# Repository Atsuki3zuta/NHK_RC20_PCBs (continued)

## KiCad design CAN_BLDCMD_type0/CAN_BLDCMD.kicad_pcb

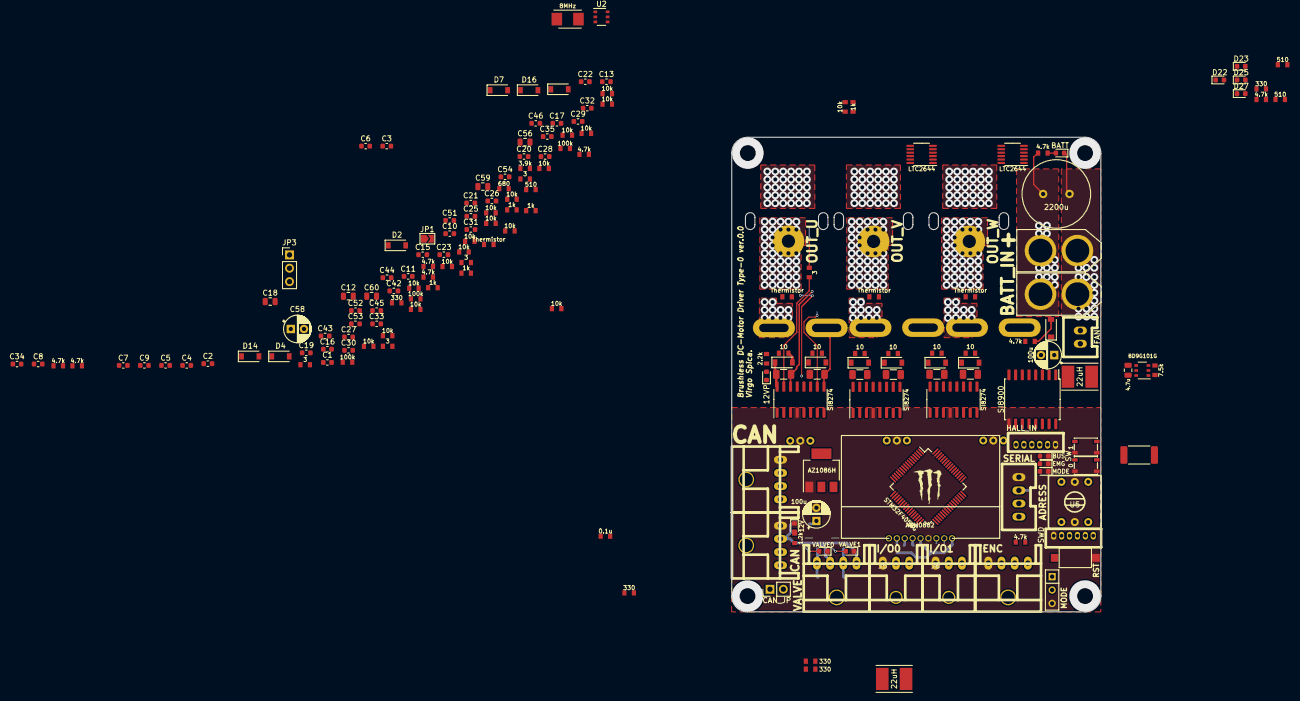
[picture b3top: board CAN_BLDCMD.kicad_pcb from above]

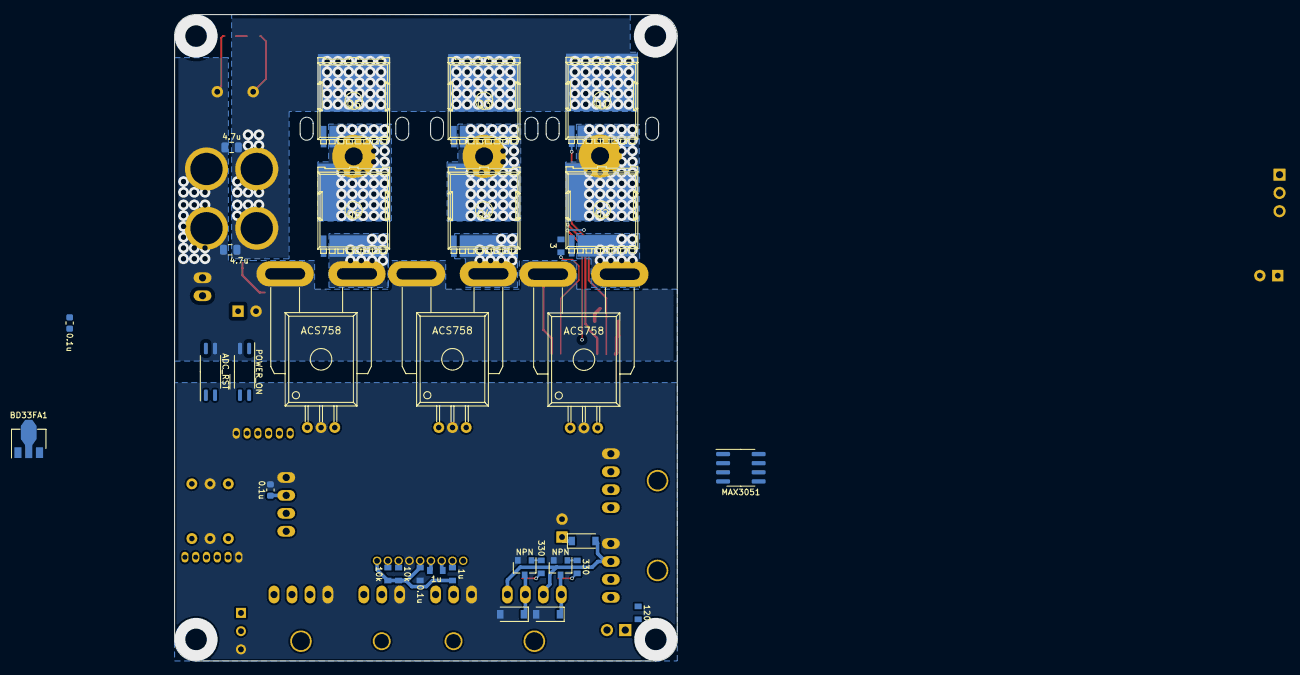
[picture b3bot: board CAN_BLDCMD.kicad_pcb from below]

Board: 2 copper layers, 70.0 x 90.0 mm, 215 parts (31 on the bottom side), 136 nets.

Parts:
C1, C2: 22p; C_0603_1608Metric
C3, C4, C5, C6, C7, C8, C9, C10, C11, C20, C22, C23, C24, C25, C26, C27, C28, C29, C33, C34, C35, C42, C43, C44, C45, C46, C47, C51, C52, C53, C54: 0.1u; C_0603_1608Metric
C12, C18, C48, C55, C56, C57, C59, C60: 4.7u; C_0805_2012Metric
C13: 1u; C_0603_1608Metric
C14, C50, C58: 100u; CP_Radial_D5.0mm_P2.50mm
C15, C17: 2.2u; C_0603_1608Metric
C16: 4.7u; C_0603_1608Metric
C19: 10u; C_0603_1608Metric
C21: 22u; C_0603_1608Metric
C30, C31, C32: 470n; C_0603_1608Metric
C36, C37, C38, C39, C40, C41: 4.7u; C_1206_3216Metric
C49: 2200u; C_Radial_D13mm_H25.0mm_P5.00mm
C61, C62: 1u; 1608_WP
C63, C64: 0.1u; 1608_WP
D1, D2, D3, D4, D7, D8, D9, D10, D11, D12, D13, D14, D15, D16, D17, D18: DIODE; D_SOD-123
D5: BUS; LED_0603_1608Metric
D6: EMG; LED_0603_1608Metric
D19: VALVE0; LED_0603_1608Metric
D20: VALVE1; LED_0603_1608Metric
D21: 12V; LED_0603_1608Metric
D22: 5V; LED_0603_1608Metric
D23: 3V3; LED_0603_1608Metric
D24: BATT; LED_0603_1608Metric
D25: MAIN_BATT; LED_0603_1608Metric
D26: 12VP; LED_0603_1608Metric
D27: 3V3P; LED_0603_1608Metric
D28: MODE; LED_0603_1608Metric
J1: SWD; ZH_6P
J2, J3: CAN; XA_4L
J4: ENC; XA_4L
J5: I/O0; XA_3L
J6: I/O1; XA_3L
J7: SERIAL; XA_4P
J8: FAN; XA_2P
J9: BATT_IN; XT60_F
J10: BATT_IN; XT60_M
J11: OUT_U; SolderWirePad_1x01_Drill2.5mm
J12: OUT_V; SolderWirePad_1x01_Drill2.5mm
J13: OUT_W; SolderWirePad_1x01_Drill2.5mm
J14: VALVE; XA_4L
J15: HALL_IN; ZH_6P
JP1: SWD_JP; SolderJumper-2_P1.3mm_Open_TrianglePad1.0x1.5mm
JP2: CAN_JP; PinHeader_1x02_P2.54mm_Vertical
JP3: I/O_Vdd; PinHeader_1x03_P2.54mm_Vertical
L1, L2: 22uH; Inductor_Taiyo-Yuden_NR-50xx_HandSoldering
Q1, Q2, Q3, Q4, Q5, Q6: MOSFET_N; HSOF-8-1
Q7, Q8: NPN; SOT-23
R1, R5, R6, R7, R11, R15, R16, R17, R18, R19, R23, R24, R25, R26, R48, R50, R52, R54, R55, R65: 10k; 1608_WP
R2: 3.9k; 1608_WP
R3: 680; 1608_WP
R4: 120; 1608_WP
R8, R9, R28, R29, R30, R31, R32, R61, R62: 4.7k; 1608_WP
R10, R12, R49, R51, R53: 1k; 1608_WP
R13, R14, R27, R56, R57, R60, R66: 330; 1608_WP
R20, R21, R22: 100k; 1608_WP
R33, R34, R35, R36, R37, R38: 3; 1608_WP
R39, R40, R41, R42, R43, R44: 10; 1608_WP
R45: 7.5k; 1608_WP
R46, R59, R64: 510; 1608_WP
R47: 47; R_2512_6332Metric
R58: 1.2k; 1608_WP
R63: 2.2k; 1608_WP
SW1: SW0; SW_SPST_PTS810
SW2: SW1; SW_SPST_PTS810
SW3: RST; SW_SPST_CK_RS282G05A3
SW4: MODE; SW_Micro_SPST
TH1, TH2, TH3, TH4: Thermistor; 1608_WP
U1: MAX3051; SOIC-8_3.9x4.9mm_P1.27mm
U2, U15: BD9G101G; TSOP-6_1.65x3.05mm_P0.95mm
U3: STM32F405RG; LQFP-64_10x10mm_P0.5mm
U4: AZ1086H; SOT-223-3_TabPin2
U5: ADRESS; rotary_0F
U6: POWER_ON; SOIC-4_4.55x2.6mm_P1.27mm
U7, U8, U9: SI8274; SOIC-16_3.9x9.9mm_P1.27mm
U10: SI8900; SOIC-16W_7.5x10.3mm_P1.27mm
U11: ADC_~RST; SOIC-4_4.55x2.6mm_P1.27mm
U12, U13, U14: ACS758; ACS785xCB
U16, U17: LTC2644; MSOP-12_3x4mm_P0.65mm
U18: BD33FA1; SOT-89-3
U19: LOGO; Mini_Monster
U20: AQM0802; AQM0802_original
Y1: 8MHz; Crystal_SMD_5032_2Pads

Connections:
+3.3VP: C42.1, C51.1, C52.1, C53.1, C54.1, C60.1, R28.1, R64.2, U10.1, U10.2, U16.1, U16.4, U16.5, U16.7, U16.10, U17.1, U17.4, U17.5, U17.7, U17.10, U18.1
+3V3: C3.1, C5.1, C6.1, C7.1, C11.1, C13.1, C16.1, C21.1, C29.1, C33.1, C34.1, C35.1, C61.2, C63.2, D1.1, JP3.3, R7.1, R11.1, R15.1, R54.1, R55.1, R60.2, R65.1, TH1.1, TH2.1, TH3.1, TH4.1, U1.3, U3.1, U3.13, U3.19, U3.32, U3.48, U3.64, U4.2, U6.4, U7.3, U7.8, U8.3, U8.8, U9.3, U9.8, U10.10, U10.16, U12.1, U13.1, U14.1, U20.5, U20.9
+5V: C19.1, C20.2, C24.2, D4.1, J4.2, J7.2, J15.6, JP3.1, R10.2, R12.2, R59.2, U4.3
+12P: C58.1, C59.1, D16.1, R39.1, R40.1, R41.1, R42.1, R43.1, R44.1, R63.2, U18.3
+12V: C9.1, C10.1, D3.2, J2.2, J3.2, J14.2, J14.4, R58.2
+BATT: C49.1, C55.1, C57.1, D15.2, J9.2, J10.2, Q1.D, Q3.D, Q5.D, R32.1, R61.2
+Batt: C48.1, C50.1, D15.1, R47.2, R62.2, U15.4, U15.5
/ADC_~RST~_Pin: U3.53, U11.1
/ADRESS_0: U3.29, U5.3
/ADRESS_1: U3.30, U5.1
/ADRESS_2: U3.33, U5.4
/ADRESS_3: U3.34, U5.6
/CAN1_RX: U1.4, U3.62
/CAN1_TX: U1.1, U3.61
/CAN_H: J2.3, J3.3, R4.2, U1.7
/CAN_L: J2.4, J3.4, JP2.2, U1.6
/Drive_U_Temp: C25.1, R16.1, TH1.2, U3.14
/Drive_V_Temp: C26.1, R17.1, TH2.2, U3.10
/Drive_W_Temp: C27.1, R18.1, TH3.2, U3.8
/Enable: R20.1, R21.1, R22.1, U7.5, U8.5, U9.5
/FB_5V: C4.1, C18.1, D4.2, L1.2, R2.1
/FB_12P: C43.2, C56.1, D16.2, L2.2, R45.1
/HALL_0: J15.2, U3.38
/HALL_1: J15.3, U3.39
/HALL_2: J15.4, U3.40
/I2Cx_SCL: R54.2, U20.8
/I2Cx_SDA: R55.2, U20.7
/IO0_Pin: J5.3, U3.35
/IO1_Pin: J6.3, U3.36
/LED0: R13.1, U3.50
/LED1: R14.1, U3.58
/LED2: R66.1, U3.59
/OSC_IN: C1.1, U3.5, Y1.1
/OSC_OUT: C2.1, U3.6, Y1.2
/OUT_U: C36.2, J11.1, Q1.S, Q2.D, R48.1, U7.14
/OUT_U_Analog: U10.3, U16.2
/OUT_U_Current: C30.2, R29.2, U3.15
/OUT_U_DIGITAL<3V3P: C44.2, R48.2, R49.1, U16.9
/OUT_V: C38.2, J12.1, Q3.S, Q4.D, R50.1, U8.14
/OUT_V_Analog: U10.4, U16.3
/OUT_V_Current: C31.2, R30.2, U3.11
/OUT_V_DIGITAL<3V3P: C45.2, R50.2, R51.1, U16.8
/OUT_W: C40.2, J13.1, Q5.S, Q6.D, R52.1, U9.14
/OUT_W_Analog: U10.5, U17.2
/OUT_W_Current: C32.2, R31.2, U3.9
/OUT_W_DIGITAL<3V3P: C46.2, R52.2, R53.1, U17.9
/PWR_ON_Pin: R26.1, U3.55, U6.3
/SW0: R7.2, SW1.2, U3.2
/SW1: R11.2, SW2.2, U3.3
/SWCLK: J1.3, U3.49
/SWDIO: J1.4, U3.46
/SW_MODE: R65.2, SW4.2, U3.37
/Subscribe_Temp: C28.1, R19.1, TH4.2, U3.17
/TIMx_CH1: R5.2, R9.2, U3.56
/TIMx_CH2: R6.2, R8.2, U3.57
/USARTX_RX: J7.4, U3.43
/USARTX_TX: J7.3, U3.42
/USARTx_RX: U3.52, U10.12
/USARTx_TX: U3.51, U10.13
/VALVE_0: Q7.1, R56.1
/VALVE_1: Q8.1, R57.1
/~RST: C64.2, J1.5, SW3.2, U3.7
GND: C1.2, C2.2, C3.2, C5.2, C6.2, C7.2, C9.2, C10.2, C11.2, C12.2, C13.2, C14.2, C15.2, C16.2, C17.2, C18.2, C19.2, C20.1, C21.2, C22.1, C23.1, C24.1, C25.2, C26.2, C27.2, C28.2, C29.2, C30.1, C31.1, C32.1, C33.2, C34.2, C35.2, C63.1, C64.1, D2.2, D5.1, D6.1, D17.2, D18.2, D19.1, D20.1, D21.1, D22.1, D23.1, D28.1, J1.1, J2.1, J3.1, J4.1, J5.1, J6.1, J7.1, J15.1, Q7.2, Q8.2, R1.2, R3.2, R5.1, R6.1, R16.2, R17.2, R18.2, R19.2, R20.2, R21.2, R22.2, R23.2, R24.2, R25.2, R26.2, R27.2, SW1.1, SW2.1, SW3.1, SW4.3, U1.2, U1.5, U1.8, U2.2, U3.12, U3.18, U3.63, U4.1, U5.2, U5.5, U7.4, U8.4, U9.4, U10.9, U12.2, U13.2, U14.2, U20.6
GNDPWR: C37.2, C39.2, C41.2, C42.2, C44.1, C45.1, C46.1, C48.2, C49.2, C50.2, C51.2, C52.2, C53.2, C54.2, C55.2, C56.2, C57.2, C58.2, C59.2, C60.2, D14.2, D24.1, D25.1, D26.1, D27.1, J8.1, J9.1, J10.1, R46.2, R49.2, R51.2, R53.2, U6.2, U7.9, U8.9, U9.9, U10.8, U11.3, U12.5, U13.5, U14.5, U15.2, U16.6, U16.11, U16.12, U17.6, U17.11, U17.12, U18.2
IO_Vdd: C22.2, C23.2, D7.1, J5.2, J6.2
unnamed: C4.2, R2.2, R3.1, U2.3
unnamed: C8.1, D2.1, L1.1, U2.6
unnamed: C8.2, U2.1
unnamed: C12.1, C14.1, D3.1, U2.4, U2.5
unnamed: C15.1, U3.31
unnamed: C17.1, U3.47
unnamed: C36.1, D8.1, U7.16
unnamed: C37.1, D9.1, U7.11
unnamed: C38.1, D10.1, U8.16
unnamed: C39.1, D11.1, U8.11
unnamed: C40.1, D12.1, U9.16
unnamed: C41.1, D13.1, U9.11
unnamed: C43.1, R45.2, R46.1, U15.3
unnamed: C47.1, D14.1, L2.1, U15.6
unnamed: C47.2, U15.1
unnamed: C61.1, U20.2
unnamed: C62.1, U20.3
unnamed: C62.2, U20.4
unnamed: D1.2, JP1.2
unnamed: D5.2, R13.2
unnamed: D6.2, R14.2
unnamed: D7.2, JP3.2
unnamed: D8.2, R39.2
unnamed: D9.2, R40.2
unnamed: D10.2, R41.2
unnamed: D11.2, R42.2
unnamed: D12.2, R43.2
unnamed: D13.2, R44.2
unnamed: D17.1, J14.1, Q7.3
unnamed: D18.1, J14.3, Q8.3
unnamed: D19.2, R56.2
unnamed: D20.2, R57.2
unnamed: D21.2, R58.1
unnamed: D22.2, R59.1
unnamed: D23.2, R60.1
unnamed: D24.2, R61.1
unnamed: D25.2, R62.1
unnamed: D26.2, R63.1
unnamed: D27.2, R64.1
unnamed: D28.2, R66.2
unnamed: J1.2, JP1.1
unnamed: J4.3, R8.1, R12.1
unnamed: J4.4, R9.1, R10.1
unnamed: J8.2, R47.1
unnamed: JP2.1, R4.1
unnamed: Q1.G, R33.1
unnamed: Q2.G, R34.1
unnamed: Q2.S, U12.4
unnamed: Q3.G, R35.1
unnamed: Q4.G, R36.1
unnamed: Q4.S, U13.4
unnamed: Q5.G, R37.1
unnamed: Q6.G, R38.1
unnamed: Q6.S, U14.4
unnamed: R1.1, U3.60
unnamed: R15.2, U3.28
unnamed: R23.1, U7.6
unnamed: R24.1, U8.6
unnamed: R25.1, U9.6
unnamed: R27.1, U11.2
unnamed: R28.2, U10.7, U11.4
unnamed: R29.1, U12.3
unnamed: R30.1, U13.3
unnamed: R31.1, U14.3
unnamed: R32.2, U6.1
unnamed: R33.2, U7.15
unnamed: R34.2, U7.10
unnamed: R35.2, U8.15
unnamed: R36.2, U8.10
unnamed: R37.2, U9.15
unnamed: R38.2, U9.10

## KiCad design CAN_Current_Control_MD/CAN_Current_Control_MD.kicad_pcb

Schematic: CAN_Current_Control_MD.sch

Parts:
C1, C8, C11, C12, C19, C20, C21, C22, C23, C24, C28, C31, C32, C33, C34, C35, C36, C38, C39, C40, C41, C42, C55, C56: 0.1u; 1608_WP
C2, C5, C25, C43, C44, C45, C46, C47, C52, C53: 4.7u; C_0805_2012Metric
C3, C4: 22p; 1608_WP
C6, C7, C9, C10, C37, C54: 0.1u; C_0603_1608Metric
C13, C26, C27: 1u; 1608_WP
C14, C16: 2.2u; 1608_WP
C15: 4.7u; 1608_WP
C17: 10u; 1608_WP
C18: 22u; 1608_WP
C29, C49: 10u; C_0805_2012Metric
C30, C48, C50: 100u; CP_Radial_D5.0mm_P2.50mm
C51: 1500u; C_Radial_D13mm_H25.0mm_P5.00mm
D1: 12V; 1608_WP
D2: 3V3; 1608_WP
D3, D11, D14, D15, D16, D17, D18, D19, D20, D21, D22, D24, D26: DIODE; D_SOD-123
D4: BATT; LED_0603_1608Metric
D5: MAIN_BATT; LED_0603_1608Metric
D6: 12VP; LED_0603_1608Metric
D7: 5VP; LED_0603_1608Metric
D8: 3V3P; LED_0603_1608Metric
D9: EMG0; 1608_WP
D10: BUS0; 1608_WP
D12: EMG1; 1608_WP
D13: BUS1; 1608_WP
D23: DIODE; D_SMA
D25: VALVE0; LED_0603_1608Metric
D27: VALVE1; LED_0603_1608Metric
F1: Polyfuse; Fuse_1812_4532Metric_Pad1.30x3.40mm_HandSolder
J1: SWD; ZH_6P
J2, J3: CAN; XA_4L
J4: ENC0; XA_4L
J5: ENC1; XA_4L
J6: I/O_0; XA_3L
J7: I/O_1; XA_3L
J8: BATT_IN; XT60_F
J9: BATT_IN; XT60_M
J10: FAN; XA_2P
J11: OUT_0; XT60_F
J12: OUT_1; XT60_F
J13: VALVE; XA_4L
JP1: SWD_JP; SolderJumper-2_P1.3mm_Open_TrianglePad1.0x1.5mm
JP2: CAN_JP; PinHeader_1x02_P2.54mm_Vertical
JP3: I/O_Vdd; PinHeader_1x03_P2.54mm_Vertical
L1, L2: 22uH; Inductor_Taiyo-Yuden_NR-50xx_HandSoldering
Q1, Q2, Q3, Q4, Q5, Q6, Q7, Q8: MOSFET_N; D2-PAK_compact
Q9, Q10: NPN; SOT-23
R1: 2.2k; 1608_WP
R2, R6: 510; 1608_WP
R3, R4: 4.7k; R_0603_1608Metric
R5: 2.2k; R_0603_1608Metric
R7, R63, R64: 330; 1608_WP
R8, R9, R10, R31: 10k; R_0603_1608Metric
R11, R12, R13, R14: 240; R_0603_1608Metric
R15: 120; R_0603_1608Metric
R16, R17, R18, R19, R30, R32, R33, R34, R35, R36, R38, R39, R41, R43, R45, R47: 10k; 1608_WP
R20, R21, R22, R23: 4.7k; 1608_WP
R24, R25, R26, R27, R37: 1k; 1608_WP
R28: 3.9k; R_0603_1608Metric
R29: 680; R_0603_1608Metric
R40, R42, R44, R46: 10; 1608_WP
R48: 7.5k; R_0603_1608Metric
R49: 510; R_0603_1608Metric
R50, R51, R52, R53, R54, R55, R56, R57: 3; R_0603_1608Metric
R58, R59, R60, R61: 2m; R_2010_5025Metric
R62: 47; R_2812
SW1: SW0; SW_SPST_CK_RS282G05A3
SW2: SW1; SW_SPST_CK_RS282G05A3
SW3: RST; SW_SPST_CK_RS282G05A3
TH1, TH2, TH3, TH4, TH5: Thermistor; 1608_WP
U1: BD33FA1; SOT-89-3
U2: ISO1050DUB; SOP-8_6.62x9.15mm_P2.54mm
U3: STM32F405RG; LQFP-64_10x10mm_P0.5mm
U4: ADRESS; rotary_0F
U5: AZ1086H; SOT-223-3_TabPin2
U6, U12: BD9G101G; TSOP-6_1.65x3.05mm_P0.95mm
U7: AQM0802; AQM0802_original
U8, U9, U10, U11: NCP5104; SOIC-8_3.9x4.9mm_P1.27mm
U13, U14: INA181A1; SOT-23-6
U15: LOGO; Mini_Monster
Y1: 8MHz; Crystal_SMD_5032_2Pads

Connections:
+3.3VP: C6.1, C7.1, C8.1, C11.1, C12.1, C13.1, C15.1, C26.2, C28.2, C55.1, C56.1, D3.1 (K), D14.1 (K), JP3.1, R7.2, R11.1, R12.1, R13.1, R14.1, R30.2, R31.1, R32.2, TH1.1, TH2.1, TH3.1, TH4.1, TH5.1, U2.1 (VCC1), U3.1 (VBAT), U3.13 (VDDA), U3.19 (VDD), U3.32 (VDD), U3.48 (VDD), U3.64 (VDD), U7.5, U7.9, U13.6 (V+), U14.6 (V+)
+3V3: C1.1, C5.1, R2.2, U1.1, U2.8 (VCC2)
+12P: C25.1, C50.1, D6.2, D22.1 (K), J13.2, J13.4, R40.2, R42.2, R44.2, R46.2, U6.4, U6.5
+12V: C2.1, D11.1 (K), R1.2, U1.3
+BATT: C51.1, C52.1, C53.1, D23.2, J8.2, J9.2, Q1.D, Q3.D, Q5.D, Q7.D, R3.2
/ADRESS_1: U3.23 (ADC12_IN7/TIM1_CH1N/TIM8_CH1N/TIM14_CH1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), U4.3
/ADRESS_2: U3.27 (ADC12_IN9/TIM1_CH3N/TIM8_CH3N/TIM3_CH4/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), U4.1
/ADRESS_4: U3.21 (ADC12_IN5/TIM2_CH1_ETR/TIM8_CH1N/PA5), U4.4
/ADRESS_8: U3.22 (ADC12_IN6/TIM3_CH1/TIM13_CH1/PA6), U4.6
/BATTERY_VOLTAGE: C34.1, R36.2, R37.1, U3.15 (UART4_RX/ADC12_IN1/TIM5_CH2/TIM2_CH2/PA1)
/CAN1_RX: U2.2 (RXD), U3.61 (TIM4_CH3/TIM10_CH1/CAN1_RX/PB8)
/CAN1_TX: U2.3 (TXD), U3.62 (TIM4_CH4/TIM11_CH1/CAN1_TX/PB9)
/CAN_H: J2.3, J3.3, JP2.1, U2.7 (CANH)
/CAN_L: J2.4, J3.4, R15.1, U2.6 (CANL)
/Current0_Analog: U3.10 (PC2/ADC12_IN12), U13.1
/Current1_Analog: U3.11 (PC3/ADC12_IN13), U14.1
/EN0: R41.1, R43.1, U3.37 (PC6/TIM8_CH1/USART6_TX/TIM3_CH1), U8.3 (~SD), U9.3 (~SD)
/EN1: R45.1, R47.1, U3.34 (TIM1_CH1N/CAN2_TX/PB13), U10.3 (~SD), U11.3 (~SD)
/FB_5V: C29.1, C30.1, D16.2 (A), L1.2, R28.1
/FB_12V: C49.1, D22.2 (A), L2.2, R48.1
/I2C2_SCL: R30.1, U3.29 (USART3_TX/TIM2_CH3/PB10), U7.8
/I2C2_SDA: R32.1, U3.30 (USART3_RX/TIM2_CH4/PB11), U7.7
/IO_0: J6.3, U3.2 (PC13)
/IO_1: J7.3, U3.3 (PC14/OSC32_IN)
/LED0: D9.1, U3.52 (PC11/UART4_RX/USART3_RX)
/LED1: D10.1, U3.53 (PC12/UART5_TX)
/LED2: D12.1, U3.54 (PD2/UART5_RX)
/LED3: D13.1, U3.55 (TIM2_CH2/PB3)
/MD0L_Temp: C32.1, R34.1, TH2.2, U3.9 (PC1/ADC12_IN11)
/MD0R_Temp: C35.1, R38.1, TH4.2, U3.8 (PC0/ADC12_IN10)
/MD1L_Temp: C33.1, R35.1, TH3.2, U3.26 (ADC12_IN8/TIM1_CH2N/TIM8_CH2N/TIM3_CH3/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)
/MD1R_Temp: C36.1, R39.1, TH5.2, U3.25 (PC5/ADC12_IN15)
/OSC_IN: C3.1, U3.5 (OSC_IN), Y1.1
/OSC_OUT: C4.1, U3.6 (OSC_OUT), Y1.2
/PWM0L: U3.39 (PC8/TIM8_CH3/TIM3_CH3), U8.2 (IN)
/PWM0R: U3.38 (PC7/TIM8_CH2/USART6_RX/TIM3_CH2), U9.2 (IN)
/PWM1L: U3.36 (TIM1_CH3N/TIM8_CH3N/TIM12_CH2/PB15), U10.2 (IN)
/PWM1R: U3.35 (TIM1_CH2N/TIM8_CH2N/TIM12_CH1/PB14), U11.2 (IN)
/SW0: R8.2, SW1.2, U3.40 (PC9/TIM8_CH4/TIM3_CH4)
/SW1: R10.2, SW2.2, U3.41 (TIM1_CH1/PA8)
/SWCLK: J1.3, U3.49 (SWCLK/PA14)
/SWDIO: J1.4, U3.46 (SWDIO/PA13)
/Substrate_Temp: C31.1, R33.1, TH1.2, U3.20 (ADC12_IN4/PA4)
/TIM3_CH1: R17.2, R21.2, U3.56 (TIM3_CH1/PB4)
/TIM3_CH2: R19.2, R23.2, U3.57 (CAN2_RX/TIM3_CH2/PB5)
/TIM4_CH1: R16.2, R20.2, U3.58 (TIM4_CH1/CAN2_TX/USART1_TX/PB6)
/TIM4_CH2: R18.2, R22.2, U3.59 (USART1_RX/TIM4_CH2/PB7)
/USART1_RX: U3.43 (USART1_RX/TIM1_CH3/PA10)
/USART1_TX: U3.42 (USART1_TX/TIM1_CH2/PA9)
/VALVE0: Q9.1, R63.1
/VALVE1: Q10.1, R64.1
/~RST: C54.1, J1.5, SW3.2, U3.7 (~RST)
Batt: C47.1, C48.1, D23.1, R4.2, R36.1, R62.2, U12.4, U12.5
GND: C1.2, C2.2, C5.2, C9.1, C10.1, D1.1, D2.1, J2.1, J3.1, U1.2, U2.5 (GND2)
GNDPWR: C3.2, C4.2, C6.2, C7.2, C8.2, C11.2, C12.2, C13.2, C14.2, C15.2, C16.2, C17.2, C18.2, C19.2, C20.1, C21.1, C23.1, C24.1, C25.2, C28.1, C29.2, C30.2, C31.2, C32.2, C33.2, C34.2, C35.2, C36.2, C37.2, C38.2, C39.2, C40.2, C41.2, C47.2, C48.2, C49.2, C50.2, C51.2, C52.2, C53.2, C54.2, C55.2, C56.2, D4.1, D5.1, D7.1, D8.1, D15.2 (A), D21.2 (A), D24.2 (A), D25.1, D26.2 (A), D27.1, J1.1, J4.1, J5.1, J6.1, J7.1, J8.1, J9.1, J10.1, Q9.2, Q10.2, R5.1, R9.2, R16.1, R17.1, R18.1, R19.1, R29.2, R33.2, R34.2, R35.2, R37.2, R38.2, R39.2, R41.2, R43.2, R45.2, R47.2, R49.2, R58.1, R59.1, R60.1, R61.1, SW1.1, SW2.1, SW3.1, U2.4 (GND1), U3.12 (VSSA), U3.18 (VSS), U3.63 (VSS), U4.2, U4.5, U5.1, U6.2, U7.6, U8.4 (GND), U9.4 (GND), U10.4 (GND), U11.4 (GND), U12.2, U13.2 (GND), U13.4 (-), U13.5 (REF), U14.2 (GND), U14.4 (-), U14.5 (REF)
MD0_OUT: Q2.S, Q4.S, R58.2, R60.2, U13.3 (+)
MD1_OUT: Q6.S, Q8.S, R59.2, R61.2, U14.3 (+)
unnamed: C9.2, C10.2, D11.2 (A), J2.2, J3.2
unnamed: C14.1, U3.31 (VCAP_1)
unnamed: C16.1, U3.47 (VCAP_2)
unnamed: C18.1, D14.2 (A), U5.2
unnamed: C19.1, R28.2, R29.1, U6.3
unnamed: C22.1, D15.1 (K), L1.1, U6.6
unnamed: C22.2, U6.1
unnamed: C23.2, C24.2, J6.2, J7.2, JP3.2
unnamed: C26.1, U7.2
unnamed: C27.1, U7.3
unnamed: C27.2, U7.4
unnamed: C37.1, R48.2, R49.1, U12.3
unnamed: C38.1, D17.2 (A), R40.1, U8.1 (Vcc)
unnamed: C39.1, D18.2 (A), R42.1, U9.1 (Vcc)
unnamed: C40.1, D19.2 (A), R44.1, U10.1 (Vcc)
unnamed: C41.1, D20.2 (A), R46.1, U11.1 (Vcc)
unnamed: C42.1, D21.1 (K), L2.1, U12.6
unnamed: C42.2, U12.1
unnamed: C43.1, D17.1 (K), U8.8 (VBOOT)
unnamed: C44.1, D18.1 (K), U9.8 (VBOOT)
unnamed: C45.1, D19.1 (K), U10.8 (VBOOT)
unnamed: C46.1, D20.1 (K), U11.8 (VBOOT)
unnamed: D1.2, R1.1
unnamed: D2.2, R2.1
unnamed: D3.2 (A), JP1.2
unnamed: D4.2, R3.1
unnamed: D5.2, R4.1
unnamed: D6.1, R5.2
unnamed: D7.2, R6.1
unnamed: D8.2, R7.1
unnamed: D9.2, R11.2
unnamed: D10.2, R12.2
unnamed: D12.2, R13.2
unnamed: D13.2, R14.2
unnamed: D16.1 (K), F1.2
unnamed: D24.1 (K), J13.1, Q9.3
unnamed: D25.2, R63.2
unnamed: D26.1 (K), J13.3, Q10.3
unnamed: D27.2, R64.2
unnamed: J1.2, JP1.1
unnamed: J4.3, R22.1, R26.1
unnamed: J4.4, R20.1, R24.1
unnamed: J5.3, R23.1, R27.1
unnamed: J5.4, R21.1, R25.1
unnamed: J10.2, R62.1
unnamed: JP2.2, R15.2
unnamed: Q1.G, R50.1
unnamed: Q2.G, R51.1
unnamed: Q3.G, R52.1
unnamed: Q4.G, R53.1
unnamed: Q5.G, R54.1
unnamed: Q6.G, R55.1
unnamed: Q7.G, R56.1
unnamed: Q8.G, R57.1
unnamed: R9.1, U3.60 (BOOT0)
unnamed: R31.2, U3.28 (BOOT1/PB2)
unnamed: R50.2, U8.7 (DRV_HO)
unnamed: R51.2, U8.5 (DRV_LO)
unnamed: R52.2, U9.7 (DRV_HO)
unnamed: R53.2, U9.5 (DRV_LO)
unnamed: R54.2, U10.7 (DRV_HO)
unnamed: R55.2, U10.5 (DRV_LO)
unnamed: R56.2, U11.7 (DRV_HO)
unnamed: R57.2, U11.5 (DRV_LO)
OUT0_L: C43.2, J11.1, Q1.S, Q2.D, U8.6 (BRIDGE)
OUT0_R: C44.2, J11.2, Q3.S, Q4.D, U9.6 (BRIDGE)
OUT1_L: C45.2, J12.1, Q5.S, Q6.D, U10.6 (BRIDGE)
OUT1_R: C46.2, J12.2, Q7.S, Q8.D, U11.6 (BRIDGE)

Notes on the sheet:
PolyFuse : http://akizukidenshi.com/catalog/g/gP-10074/

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
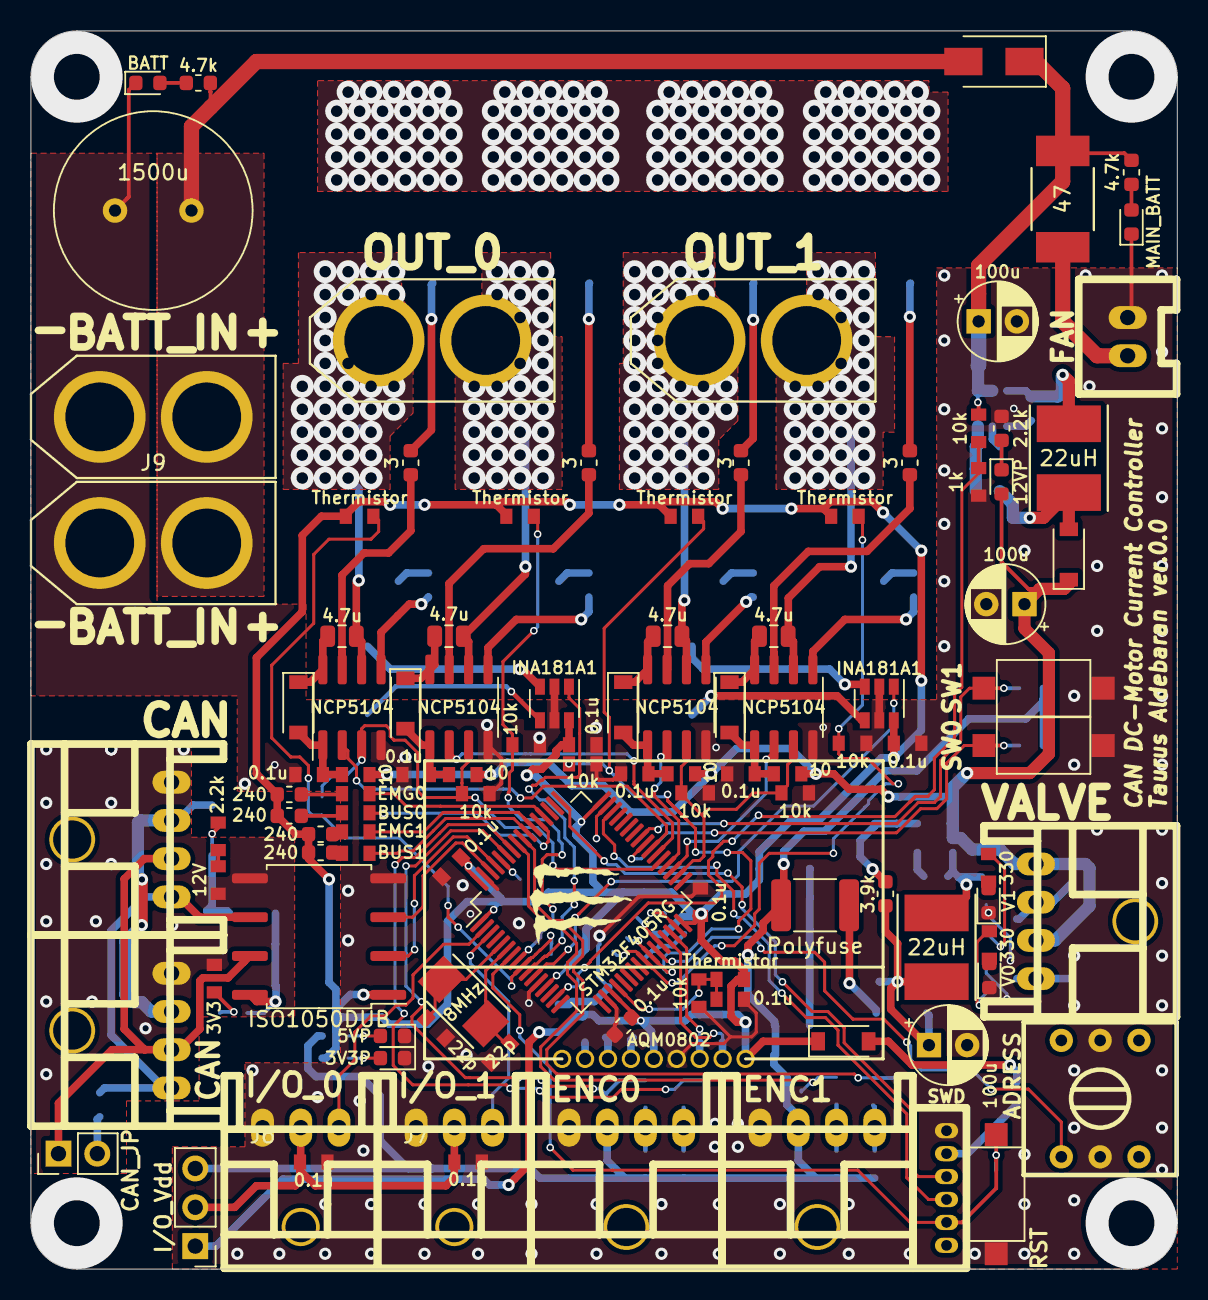
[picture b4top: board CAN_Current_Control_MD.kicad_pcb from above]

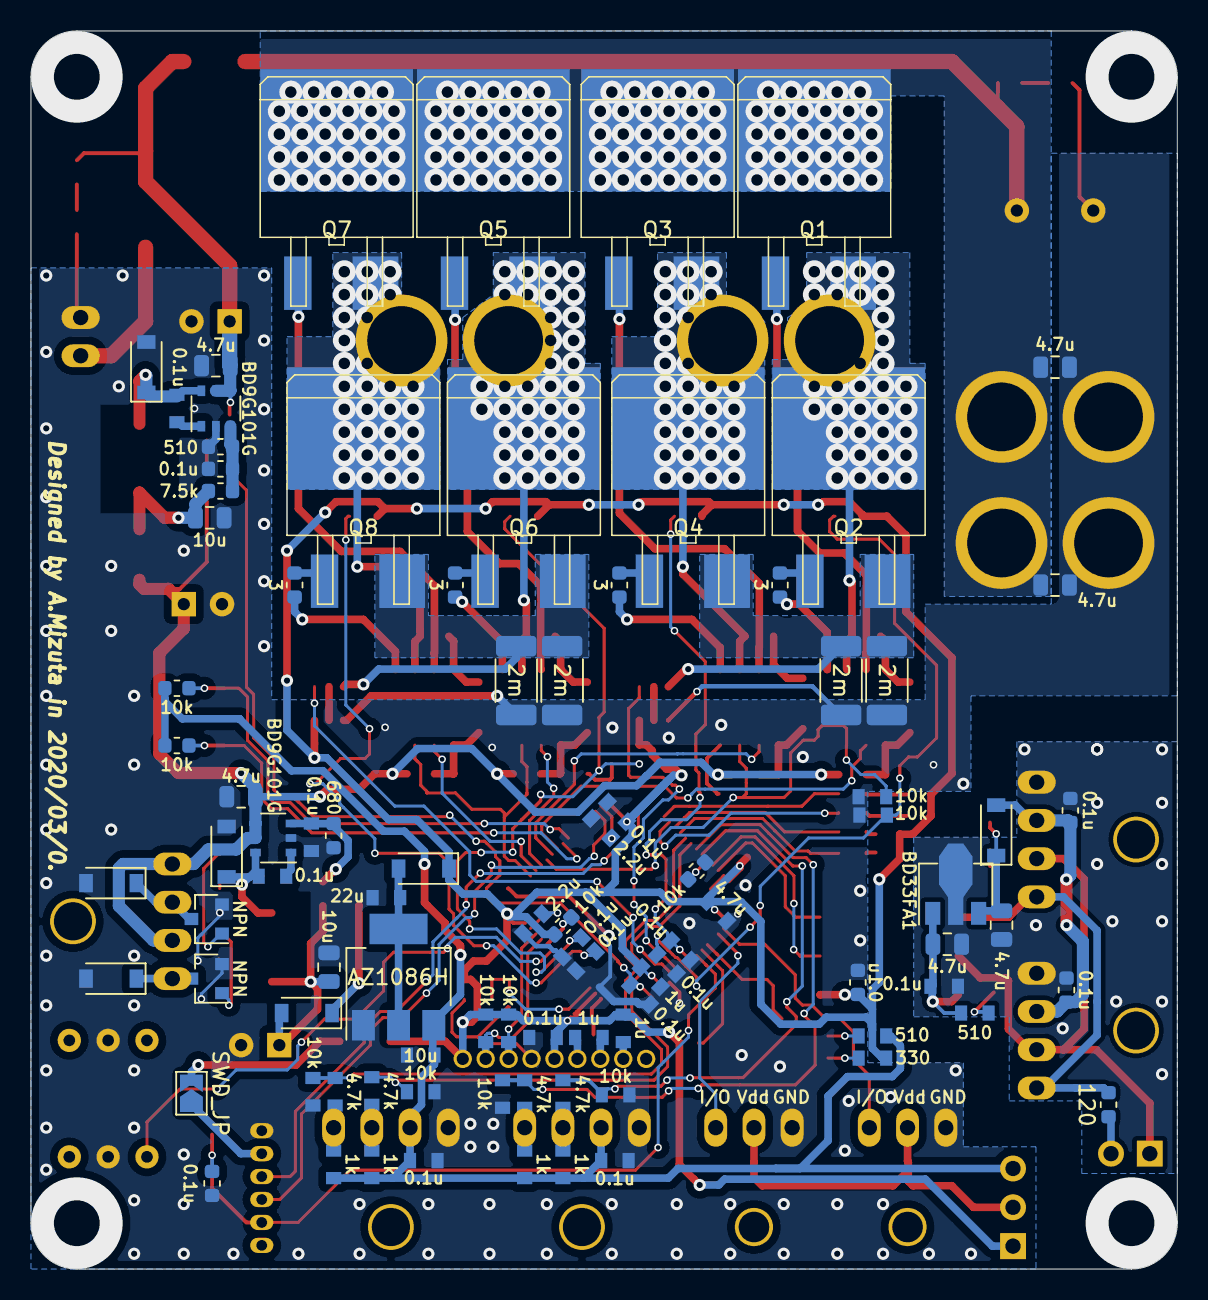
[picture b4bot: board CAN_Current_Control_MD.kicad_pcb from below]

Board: 2 copper layers, 75.0 x 81.0 mm, 200 parts (91 on the bottom side), 124 nets.
